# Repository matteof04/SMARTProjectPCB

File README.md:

# SMARTProjectPCB
The hardware part of the SMART Project.

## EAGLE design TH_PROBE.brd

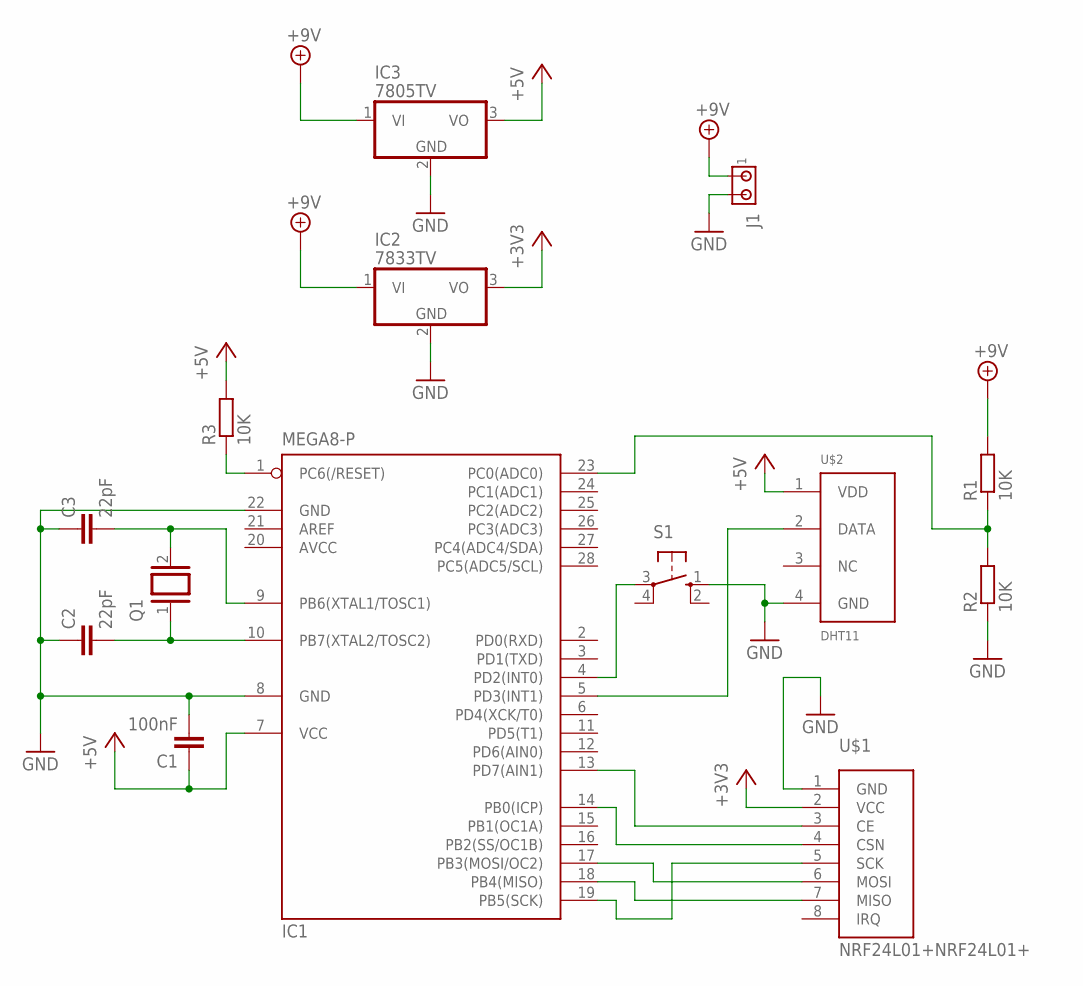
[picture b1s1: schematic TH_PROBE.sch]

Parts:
C1: 100nF; C025-025X050
C2, C3: 22pF; C025-025X050
IC1: MEGA8-P; DIL28-3
IC2: 7833TV; TO220V
IC3: 7805TV; TO220V
J1: MTA02-100; 10X02MTA
Q1: XTAL/S; QS
R1, R2, R3: 10K; 0204/7
S1: 10-XX; B3F-10XX
U$1: NRF24L01+NRF24L01+; NRF24L01+
U$2: DHT11

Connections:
+3V3: IC2.3 (VO), U$1.2 (VCC)
+5V: C1.1, IC1.7 (VCC), IC3.3 (VO), R3.2, U$2.1 (VDD)
+9V: IC2.1 (VI), IC3.1 (VI), J1.1, R1.2
AVCC: IC1.20 (AVCC)
GND: C1.2, C2.1, C3.1, IC1.8 (GND), IC1.22 (GND), IC2.2 (GND), IC3.2 (GND), J1.2, R2.1, S1.1 (S), U$1.1 (GND), U$2.4 (GND)
unnamed: IC1.17 (PB3(MOSI/OC2)), U$1.6 (MOSI)
unnamed: IC1.18 (PB4(MISO)), U$1.7 (MISO)
unnamed: C2.2, IC1.10 (PB7(XTAL2/TOSC2)), Q1.1
unnamed: C3.2, IC1.9 (PB6(XTAL1/TOSC1)), Q1.2
unnamed: IC1.19 (PB5(SCK)), U$1.5 (SCK)
unnamed: IC1.13 (PD7(AIN1)), U$1.3 (CE)
unnamed: IC1.14 (PB0(ICP)), U$1.4 (CSN)
unnamed: IC1.5 (PD3(INT1)), U$2.2 (DATA)
unnamed: IC1.23 (PC0(ADC0)), R1.1, R2.2
unnamed: IC1.4 (PD2(INT0)), S1.3
unnamed: IC1.1 (PC6(/RESET)), R3.1

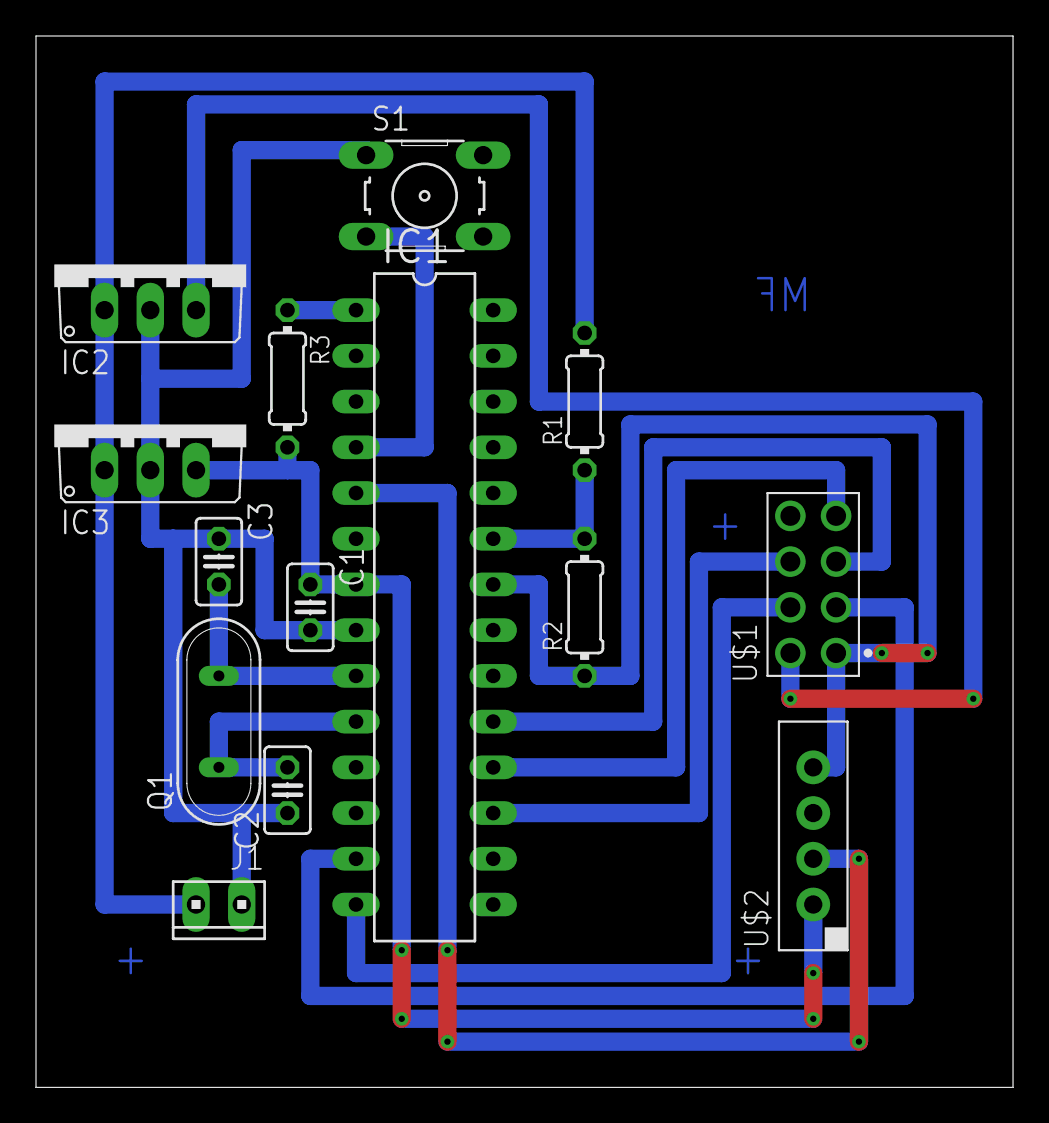
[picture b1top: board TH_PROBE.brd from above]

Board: 2 copper layers, 54.3 x 58.4 mm, 14 parts (0 on the bottom side), 15 nets.

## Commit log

2023-05-30 Added the schematics and the layouts
